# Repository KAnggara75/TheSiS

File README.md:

# TheSiS

My TheSiS for Bachelor Degree

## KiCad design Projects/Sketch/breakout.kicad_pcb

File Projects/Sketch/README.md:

A6-ESP8266-breakout
===================

This is a breakout board that includes an ESP8266 and an integrated A6 module.
It is best used with the [A6 ESP8266
library](https://github.com/skorokithakis/A6lib).

It is still incomplete, and looks like this:

## Schematic

## Board

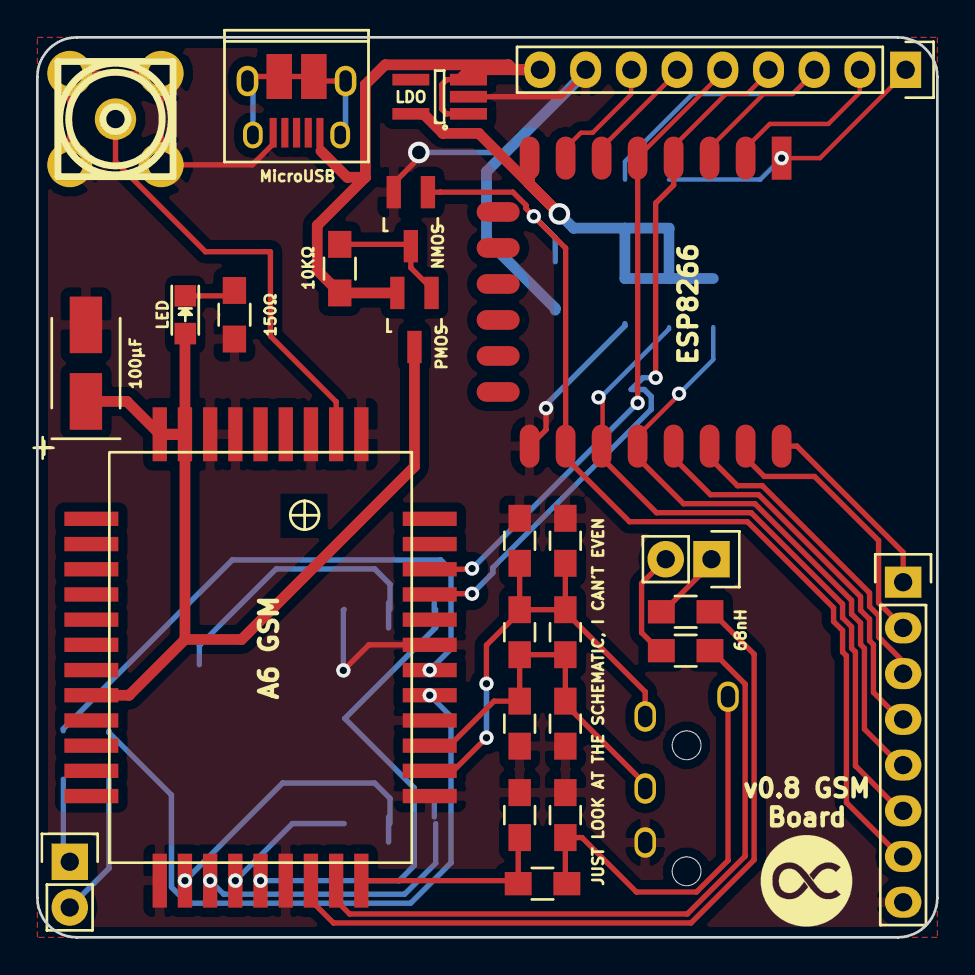
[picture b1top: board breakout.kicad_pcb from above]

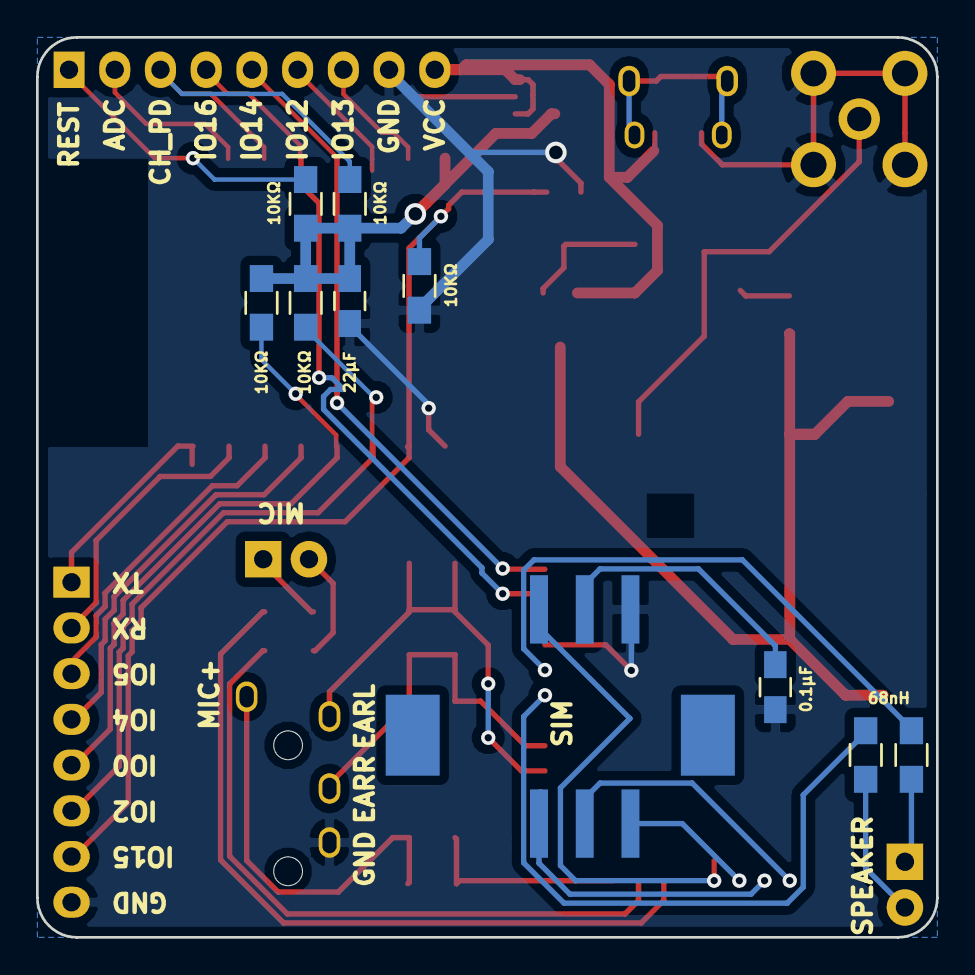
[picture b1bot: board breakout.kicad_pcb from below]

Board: 2 copper layers, 50.0 x 50.0 mm, 37 parts (10 on the bottom side), 38 nets.

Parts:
C1, C5, C9, C10, C11: 33uF; C_0805_HandSoldering
C2: 22uF; C_0805_HandSoldering
C3: 100 uF; TantalC_SizeB_EIA-3528_HandSoldering
C4: 0.1 uF; C_0805_HandSoldering
C6, C7, C8: 10uF; C_0805_HandSoldering
D1: LED; LED_0805
GSM1: A6_GSM
J1: JACK_TRS_4PINS; PJ-320L
L1, L2, L3, L4: 68nH; R_0805_HandSoldering
P1: CONN_01X08; Pin_Header_Straight_1x08
P2: SPEAKER; Pin_Header_Straight_1x02
P3: ISO7816_SIMPLE; SIM_115C_AC00_R
P4: CONN_01X09; Pin_Header_Straight_1x09
P5: SMA_CONN; sma_straight_32k101-400l5
P6: MIC; Pin_Header_Straight_1x02
P7: USB_OTG; USB_Micro-B_10103594-0001LF
Q1: Q_PMOS_GSD; SOT-23_Handsoldering
Q2: Q_NMOS_GSD; SOT-23_Handsoldering
R1, R2, R3, R4, R5, R6: 10KΩ; R_0805_HandSoldering
R7: 150Ω; R_0805_HandSoldering
R8: 68Ω; R_0805_HandSoldering
U1: SPX3819; SOT-23-5
U2: ESP-12E

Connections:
/3V3: C2.1, R1.1, R2.1, R3.1, R5.1, U1.5, U2.8
/ADC: P4.2, U2.2
/CH_PD: P4.3, R1.2, U2.3
/EARL: C6.1, C7.2, C9.1, C10.2, GSM1.23, J1.4
/EARR: C7.1, C8.2, C10.1, C11.2, GSM1.24, J1.3
/ESP_RX: GSM1.30, P4.4, U2.4
/ESP_TX: GSM1.31, P4.5, U2.5
/GPIO0: P1.5, R3.2, U2.18
/GPIO2: P1.6, R5.2, U2.17
/GPIO4: P1.4, U2.19
/GPIO5: P1.3, U2.20
/GPIO12: P4.6, U2.6
/GPIO13: P4.7, U2.7
/MIC2_P: C1.1, GSM1.21, R8.1
/PWRCTL: P1.7, Q2.1, R4.1, U2.16
/REST: P4.1, R2.2, U2.1
/RX: P1.2, U2.21
/TX: P1.1, U2.22
/VBAT: C3.1, D1.2, GSM1.8, GSM1.41, GSM1.42, Q1.3
/Vcc: P4.9, P7.1, Q1.2, R6.1, U1.1, U1.3
GND: C1.2, C2.2, C3.2, C4.1, C5.2, C6.2, C8.1, C9.2, C11.1, GSM1.13, GSM1.18, GSM1.22, GSM1.25, GSM1.28, GSM1.34, GSM1.36, GSM1.39, GSM1.40, J1.2, P1.8, P3.C4, P4.8, P5.2, P7.5, Q2.2, R4.2, R7.2, U1.2, U2.15
unnamed: C4.2, P3.C5
unnamed: C5.1, J1.5, R8.2
unnamed: D1.1, R7.1
unnamed: GSM1.14, P3.C2
unnamed: GSM1.15, P3.C3
unnamed: GSM1.16, P3.C1
unnamed: GSM1.17, P3.C6
unnamed: GSM1.19, L1.1
unnamed: GSM1.20, L2.1
unnamed: GSM1.26, L4.2
unnamed: GSM1.27, L3.2
unnamed: GSM1.35, P5.1
unnamed: L1.2, P6.1
unnamed: L2.2, P6.2
unnamed: L3.1, P2.1
unnamed: L4.1, P2.2
unnamed: Q1.1, Q2.3, R6.2

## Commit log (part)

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2019-12-19 Modifikasi Readme Mark Down
2019-12-22 Update 23 Desember 2019 (Menambah Video & Sketch Eagle)
2019-12-23 Add ESP-IDT
2019-12-23 Add IDF DIr
2019-12-25 Menghapus IDF
2020-01-01 Update 1 Januari 2020
2020-01-01 Menambakan gambar Tampilan Aplikasi
2020-01-01 Merubah Dir TheSis_App menjadi TheSiS_App pada Project
2020-01-02 Add new Screen Shoot
2020-01-02 Update Screen Shoot
2020-01-03 Add Logo & Title image file for pcb
2020-01-06 Make Folder Project ESP32
2020-01-17 Add Administratif
2020-03-23 Update 24 Maret 2020 (Menamahkan LaTex)
2020-03-23 Update LaTeX
2020-03-24 Menambahkan file Jurnal dan BAB I kedalam Proposal.docx
2020-03-24 Menghapus output LaTeX
2020-03-24 menambah ukuran huruf pada proposal.tex
2020-04-05 administratif
2020-04-05 memasukan laporan promin
2020-04-05 update proposal dan workspace
2020-04-09 menambahkan surat penajuan pembimbing
2020-04-09 memperbaharui borang 1
2020-04-09 update proposal bab 1 menjadi 4 paragraf
2020-04-10 Menambahkan Jurnal
2020-04-10 update Proposal, menambahkan pararaf terakhir bab i, Penelitian terkait
2020-04-10 Menyelesaikan Latar Belakang
2020-04-10 Membuat Halaman i menhadi I-1 pada Bab I
2020-04-10 Menyelessaikan BAB I, perbaiki halaman Romawi
2020-04-15 memulai BAB II
2020-04-17 Menambahkan 2 paragraf terakhir pada BAB I
2020-04-21 Menambahkan 9 jurnal dari IEEE
2020-04-21 Ganti judul + menghapus paragraf 2
2020-04-22 Membuat Praktikum Kosentrasi Komputer
2020-04-22 Menambah BAB II 2.1. Studi Literatur
2020-04-23 Memperbaharui Rumusan Masalah
2020-05-01 + Datasheet ESP32
2020-05-01 Laporan Promin Terbaru Fix
2020-05-01 Menambahkan Mikrokontroler esp32 pada bab 2
2020-05-04 Form B2 Bukti Bebas Praktikum
2020-05-13 Menambah temlate artikel Sitekin
2020-05-13 Gambar power skema ESP32
2020-05-13 Merubah kata Extensa menjadi Xtensa, Menambahkan sub bab µP
2020-05-13 Menambahkan prosesor 2.2.1. Xtensa LX6
2020-05-13 Menambahkan uC
2020-05-13 datasheet dan gambar up
2020-05-19 Gambar ESP32
2020-05-19 Jurnal Post-RISC
2020-05-19 Update 19 Mei 2020
2020-05-19 Menambahkan Gamar SIM800L
2020-05-19 Menyelesaikan Sub Bab SIM800L
2020-05-20 Menambah file gambar
2020-05-20 Menyelesaikan SIM800L, GPS, Akselerometer dan modul relay (SUB BAB)
2020-05-21 Menyelesaikan Sub Bab Dataase
2020-05-21 + Logo Android 2019
2020-05-21 Menyelesaikan sub bab android
2020-05-26 Memulai BAB III
2020-05-26 Menambah File Flowchart
2020-05-26 Membuat case 3D
2020-05-28 git Ignore Poster & stensa.pdf
2020-05-29 Tambah Gambar
2020-05-29 Menghapus file blok siagram pada folder project/sketch/kanggara75
2020-05-29 Perbaiki gambar flowchart hardware
2020-05-29 Update file flowchart
2020-05-29 ++ Ilustrasi sistem
2020-05-29 menmbah gambar dengan resolusi yg lebih rendah
2020-05-29 memperkecil resolusi gambar
2020-05-29 memperkecik resolusi gambar => memperkecil file size
2020-05-31 Finishing, tinggal daftar isi dkk
2020-05-31 Sebelum editing Italic
2020-05-31 Upload classroom *Finish*
2020-06-01 revisi 0.1
2020-06-01 mengubah judul sub bab 3.8
2020-06-01 Mengubah Sub Judul 3.8
2020-06-07 Revisi 08 Juni 2020 1. Merubah sub bab 3.8. menjadi Skenario Pengujian 2. Menambah Gambar halaman utama aplikasi 3. Menambah Referensi Skripsi (Tahun 2017 & 2019) 4. Menggabungkan poin poin pada rumu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
2020-06-10 Menambahkan Java. Proposal.docx
2020-06-15 Menyelesaikan Borang 1
2020-06-15 step ke borang 2
2020-06-15 Progres Untuk Borang 2 (TTD bimingan dan penunjukan pembimbing)
2020-06-25 TTD Borang 2
2020-06-25 Menyelesaikan Borang 2
2020-06-25 Menyelesaikan Pra Seminar
2020-06-25 Memasukan KHS dan Transkrip Kedalam Folder
2020-06-25 Memasukan Penunjukan Pembimbing Kedalam Folder Yg lama DImasukan Dalam file.rar
2020-06-25 Rar File Borang 1
2020-06-25 Penunjukan Penguji Selesai
2020-06-25 Update Flowchart
2020-07-21 borang 2 post seminar
2020-07-21 Borang Hasil Seminar
2020-07-21 Menghapus Jurnal Artikel Sitekin
2020-07-21 Revisi 21.07.2001
2020-07-21 Revisi 21.07.2002 (Smart Early System)
2020-07-24 Selesai Revisi Penguji Taap 1 (24.07.2001)
2020-07-24 Gambar + Flowchart + Jurnal
2020-08-20 21.08.2001 (Selesai Seminar + Berita Acara)
2020-08-23 Menghapus file tidak penting
2020-08-23 Template Jurnal JOIN
2020-08-23 menghapus latex
2020-09-30 update template jurnal
2020-09-30 Add Manajemant Waktu
2020-09-30 add JST Template v2
2020-09-30 Selesai Mikro....
2020-10-03 Rename Jurnal dkk to Reference
2020-10-03 sama seperti sebelumnya
2020-10-03 Arsipkan Folder Borang_01
2020-10-03 menghapus folder borang 2
2020-10-03 arsipkan file setelah seminar
2020-10-03 arsipkan folder pra seminar
2020-10-03 menambahkan undangan dan penunjukan pembombing dalam folder jilid 1
2020-10-03 menambahkan File logo baru
2020-10-03 meindahkan SKBB
2020-10-03 skematik untuk power supply
2020-10-03 Add database untuk thesis web
2020-10-03 rename folder 3d => thesis _3d
2020-10-03 Rename HW_Design => Thesis_HW
2020-10-03 remove unused file [041020]
2020-10-15 Add TheSiS_bot [Telegram Bot]
2020-10-18 Pending/Cancel Telegram Bot
2020-10-18 Accel Push POST_HTTP
2020-10-20 Finish TheSiS_HW Schematic
2020-10-21 Selesai Board v20.10.21
2020-10-21 Menamahkan Logo
2020-10-21 Finish Hardware v20.10.21
2020-10-22 Image Board Final v20.10.22
2020-10-22 Garber File v20.10.22
2020-10-22 Finish Board v20.10.20 [Order PCBWay.com]
2020-10-28 Menghapus Jurnal JOIN
2020-11-05 Perbaiki typo
2020-11-05 Sebelum install November 2020
2020-12-04 Update .gitignore and Update sql file for thesis_web project
2021-02-13 Mulai Jurnal 2021
2021-02-14 menambahkan jurnal pengukuran gps
2021-02-14 update 14 Februari 2021
2021-03-25 Update 25 Maret 2021
2021-03-30 compress file size of jurnal out
2021-03-30 Menambahkan gambar uji coba
2021-03-30 add Jurnal ref
2021-03-30 add ino file
2021-03-30 Add Jurnal Output file
2021-05-08 menambahkan hasil review
2021-06-04 menambahkan jurnal baru
2021-06-04 Update Revisi 1
2021-06-05 memindahkan contoh jurnal ke folde refrennsi
2021-06-05 Hasil Revisi ronde 2
2021-06-05 revisi 05 Juni 2021 [sitasi - belum selesai]
2021-06-12 perbaiki sitasi
2021-06-12 menyelesaikan abstrak
2021-06-14 update Simpulan 14 Juni 2021
2021-06-14 revisi hasil dan pembahasan 14 juni 2021
2022-04-15 init App
2022-04-15 init Api
2022-04-15 fix: Api folder
2022-04-21 app: init
2022-04-30 add: CODEUWSERS
2022-05-01 add: Splash with BLoC
2022-05-07 add: login from bloc
2022-05-07 add: CI/CD for app
2022-05-07 fix: git action checkout repo from v1 to v2
2022-05-07 fix: git action flutter from v2.4 to v2
2022-05-07 fix: desktop depedency protocol from git to https
2022-05-07 fix: pubspec.yaml version
2022-05-07 0.1.3 Release
2022-05-07 fix: app sign
2022-05-07 add: 0.1.5
2022-05-07 fix: gragle var
2022-05-16 Upgrade to Flutter 3
2022-06-03 upgrade laravel to 9.16.x
2022-06-03 fix: move api to standalone repo
2022-06-03 fix: move api to standalone repoi submodule
2022-06-03 fix: conditional CI/CD
2022-06-03 fix: #web folder
2022-06-03 #web deploy test1
2022-06-03 fix: remove submodule
2022-06-03 test: deploy #web
2022-06-03 test: deploy #web 2
2022-06-03 fix: web deploy server folder #web 2
2022-06-03 add: write .env file in CD
2022-06-03 #Web Deploy
2022-06-04 build(deps): bump async from 2.6.3 to 2.6.4 in /api
    Bumps [async](https://github.com/caolan/async) from 2.6.3 to 2.6.4.
    - [Release notes](https://github.com/caolan/async/releases)
    - [Changelog](https://github.com/caolan/async/blob/v2.6.4/CHANGELOG.md)
    - [Commits](https://github.com/caolan/async/compare/v2.6.3...v2.6.4)
    ---
    updated-dependencies:
2022-06-04 build(deps-dev): bump postcss from 8.4.12 to 8.4.14 in /api
    Bumps [postcss](https://github.com/postcss/postcss) from 8.4.12 to 8.4.14.
    - [Release notes](https://github.com/postcss/postcss/releases)
    - [Changelog](https://github.com/postcss/postcss/blob/main/CHANGELOG.md)
    - [Commits](https://github.com/postcss/postcss/compare/8.4.12...8.4.14)
    ---
    updated-dependencies:
2022-06-04 build(deps-dev): bump tailwindcss from 3.0.23 to 3.0.24 in /api
    Bumps [tailwindcss](https://github.com/tailwindlabs/tailwindcss) from 3.0.23 to 3.0.24.
    - [Release notes](https://github.com/tailwindlabs/tailwindcss/releases)
    - [Changelog](https://github.com/tailwindlabs/tailwindcss/blob/master/CHANGELOG.md)
    - [Commits](https://github.com/tailwindlabs/tailwindcss/compare/v3.0.23...v3.0.24)
    ---
    updated-dependencies:
2022-06-04 build(deps-dev): bump axios from 0.25.0 to 0.27.2 in /api
    Bumps [axios](https://github.com/axios/axios) from 0.25.0 to 0.27.2.
    - [Release notes](https://github.com/axios/axios/releases)
    - [Changelog](https://github.com/axios/axios/blob/v0.27.2/CHANGELOG.md)
    - [Commits](https://github.com/axios/axios/compare/v0.25.0...v0.27.2)
    ---
    updated-dependencies:
2022-06-04 build(deps-dev): bump autoprefixer from 10.4.4 to 10.4.7 in /api
    Bumps [autoprefixer](https://github.com/postcss/autoprefixer) from 10.4.4 to 10.4.7.
    - [Release notes](https://github.com/postcss/autoprefixer/releases)
    - [Changelog](https://github.com/postcss/autoprefixer/blob/main/CHANGELOG.md)
    - [Commits](https://github.com/postcss/autoprefixer/compare/10.4.4...10.4.7)
    ---
    updated-dependencies:
2022-06-04 build(deps-dev): bump laravel-mix from 6.0.43 to 6.0.46 in /api
    Bumps [laravel-mix](https://github.com/JeffreyWay/laravel-mix) from 6.0.43 to 6.0.46.
    - [Release notes](https://github.com/JeffreyWay/laravel-mix/releases)
    - [Changelog](https://github.com/laravel-mix/laravel-mix/blob/master/CHANGELOG.md)
    - [Commits](https://github.com/JeffreyWay/laravel-mix/commits)
    ---
    updated-dependencies:
2022-06-04 add: api end point
2022-06-04 fix: CODEOWNER
2022-06-04 fix: flutter widget test condition
2022-06-04 fix: git action
2022-06-05 add: api migration => finish
2022-06-06 add: API for login and board
2022-06-10 build(deps): bump guzzlehttp/guzzle from 7.4.3 to 7.4.4 in /api
    Bumps [guzzlehttp/guzzle](https://github.com/guzzle/guzzle) from 7.4.3 to 7.4.4.
    - [Release notes](https://github.com/guzzle/guzzle/releases)
    - [Changelog](https://github.com/guzzle/guzzle/blob/master/CHANGELOG.md)
    - [Commits](https://github.com/guzzle/guzzle/compare/7.4.3...7.4.4)
    ---
    updated-dependencies:
2022-06-25 add: app prepare to release
2022-06-25 fix: api #web
2022-06-25 add: docs
2022-06-25 build(deps): bump guzzlehttp/guzzle from 7.4.3 to 7.4.5 in /api
    Bumps [guzzlehttp/guzzle](https://github.com/guzzle/guzzle) from 7.4.3 to 7.4.5.
    - [Release notes](https://github.com/guzzle/guzzle/releases)
    - [Changelog](https://github.com/guzzle/guzzle/blob/master/CHANGELOG.md)
    - [Commits](https://github.com/guzzle/guzzle/compare/7.4.3...7.4.5)
    ---
    updated-dependencies:
2022-06-25 fix: update #web
2022-06-25 add: meter to km if d > 1000
2022-06-28 add: KRS
2022-06-28 add: docs for administratif
2022-07-15 add: gitignore
2022-07-20 add: bebas pustaka
2022-09-22 [ImgBot] Optimize images
    *Total -- 4,091.08kb -> 3,758.58kb (8.13%)
    /app/flutter_01.png -- 3.36kb -> 0.88kb (73.7%)
    /app/assets/icons/marker.svg -- 9.22kb -> 3.80kb (58.8%)
    /app/web/icons/Icon-maskable-512.png -- 20.51kb -> 10.54kb (48.61%)
    /app/web/icons/Icon-maskable-192.png -- 5.46kb -> 3.66kb (33.05%)
    /app/macos/Runner/Assets.xcassets/AppIcon.appiconset/app_icon_512.png -- 14.45kb -> 9.69kb (32.93%)
2022-11-28 lulus yey
2023-02-01 build(deps): bump symfony/http-kernel from 6.0.9 to 6.0.20 in /api
    Bumps [symfony/http-kernel](https://github.com/symfony/http-kernel) from 6.0.9 to 6.0.20.
    - [Release notes](https://github.com/symfony/http-kernel/releases)
    - [Changelog](https://github.com/symfony/http-kernel/blob/6.2/CHANGELOG.md)
    - [Commits](https://github.com/symfony/http-kernel/compare/v6.0.9...v6.0.20)
    ---
    updated-dependencies:
